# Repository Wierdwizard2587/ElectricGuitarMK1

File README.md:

# Electronic Guitar MK1

> A self-built, digitally-enhanced electric guitar featuring onboard effects, audio output and removable battery supply all integrated within a custom made Guitar.

---

## TL;DR Overview

- DIY portable electric guitar with integrated digital effects and modular power/audio system  
- Final version features Teensy 4.0, onboard FX, rotary encoder UI, OLED display, amp/speaker output, battery or DC power, and RGB lighting  
- Entire build: woodwork, PCBs, 3D prints, firmware, and more  
- Early prototype (Mk0) failed due to poor electrical design and overcomplex hardware, rebuilt from scratch over 12+ months with newly acquired engineering and fabrication skills  

---

## Specs (MK1)

### Hardware Features

- **Microcontroller:** Teensy 4.0 (600 MHz ARM Cortex M7, 1MB RAM)  
- **Audio Codec:** SGTL5000 via Teensy Audio Shield Rev D2  
- **Display:** 2.42" 128x64 OLED  
- **UI:** 4x rotary encoders (Adafruit I2C) with push buttons  
- **Output Options:**
  - 1W LM386 speaker amp + 8Ω speaker  
  - 3.5mm headphone jack  
  - 1/4" AUX output  
- **SD Card:** for saving and loading effect presets  

### Physical Design

- Custom red cedar guitar body with Strat-style neck and 22 frets  
- SSH passive pickup layout with 5-way selector  
- CNC acrylic panels for access and wiring  
- Modular 3D-printed brackets for internals  
- Magnetic battery bay  

### Power System

- **Battery:** 4S 18650 3500mAh Li-ion (16.8V max)  
- **BMS:** With overcharge/discharge protection  
- **Power Switching:** Automatically defaults to DC jack if plugged in  
- **Regulation:** L7805 LDO for logic, raw voltage for amp  
- **Runtime:** ~12 hours full load; much longer with optimized settings  

### RGB Lighting

- 6x WS2812B addressable LEDs  
- Controlled via UI with adjustable patterns and brightness  
- 5V from Teensy board, expandable via breakout  
- Mounted in a custom 3D enclosure with acrylic cover  
- See [Demo](https://github.com/Wierdwizard2587/ElectricGuitarMK1/raw/main/Progress%20Photos/Woodworking/IMG_9428.MOV)

### Design Decisions

- Abandoned analog FX + digipots due to impractical voltage/current handling  
- Digital FX chain implemented using Teensy Audio Library and CODEC  
- Custom single-layer PCB with JST headers for modularity  
- UI system built around I2C rotary encoders and OLED display  
- 3D-printed brackets standardized component mounting across internal assemblies  

### Tools and Processes

#### PCB Manufacturing

- **Chemical Etching:** Photoresist UV method with ferric chloride; scrapped due to accuracy and double-sided complexity  
- **CNC Milling:** Used FlatCAM to generate G-code, 3018 CNC and Candle for trace and drill cuts  

#### SMD Soldering

- **Stencil:** CNC-cut mylar sheets for paste application  
- **Soldering:** SMD components placed and reflowed on hot plate  

#### CAD and Design

- **KiCAD:** For schematic capture and board layout  
- **FreeCAD:** For PCB enclosure, LED mount, Guitar Body, Acrylic Plates/Panels and Router Jigs  

---

## Mk0 — The Failed First Attempt

The Mk0 was an ambitious retrofit of a cheap Stratocaster copy, originally sourced second-hand for $20 AUD. At the time, I had no electrical engineering knowledge and was only experienced with basic Arduino and Raspberry Pi projects.

### Body and Structural Work
- The original guitar was re-routed to fit electronics, resulting in reduced structural integrity and balance
- Body was repainted and cleaned up with minor woodworking skills from high school
- Attempted to house a Raspberry Pi, amplifier board, fans, wiring and more. all glued to plywood mounts inside the guitar

### Electronics and Power Mistakes
- Raspberry Pi 3B+ used for DSP software and effects switching via Linux keybinds
- 10x SPST buttons mapped to GPIO pins, wired manually without debounce or shielding
- Cooling: a heatsink and fan were mounted directly into the guitar body, protruding through the top
- Power: attempted to use a Makita 18V battery regulated by a voltage divider made from two 10W resistors (which exploded)
- Eventually switched to an XL6009 buck converter, mounted haphazardly on wood

### Audio and Shielding Failures
- Output sound had constant noise and interference, making the guitar unplayable
- Tried shielding the cavity with copper tape and spray enamel, but issues persisted
- Lack of analog audio knowledge led to poor layout and grounding, introducing hum and feedback

### Realization and Reset
- The experience made clear the importance of proper voltage regulation, shielding, grounding, and modular design
- Mk0 taught me the value of planning, measurement, and using the right components for audio and power
- In October 2023, I decided to scrap the build and committed to rebuilding everything from scratch

---

## The Learning Curve

To succeed with Mk1, I developed and refined skills across multiple disciplines:

- **Electrical theory and circuit design**
  - Learned core principles like Ohm’s Law, impedance, decoupling, signal paths, and analog vs digital tradeoffs by experimenting with breadboarded op-amp FX circuits and 555 timer modules.

- **Breadboarding, debugging, and perfboarding**
  - Built multiple guitar pedal-style analog effects, troubleshooting noise, biasing, and layout issues. Early soldering mistakes taught me good pad heating, proper joint inspection, and signal path discipline.

- **Custom PCB manufacturing**

  - *Chemical etching:* Photoresist and ferric chloride techniques worked for simple single-sided boards, but alignment and etch consistency were poor for complex layouts.

https://github.com/user-attachments/assets/e00821a1-996f-4fed-b84c-7d602e0a9be1

  - *CNC milling:* FlatCAM used to generate G-code from KiCAD Gerbers. I used a 3018 CNC with Candle to reliably cut traces and drill holes. Ultimately switched to ordered boards for reliability.

https://github.com/user-attachments/assets/3b78b966-fe12-4d0b-8b32-34254987f5ec

- **SMD workflow and hot plate reflow soldering**
  - Designed and cut my own mylar stencils for solder paste, allowing for precise paste application and fast assembly of SMD components on the hot plate.

- **Power systems and battery safety**
  - Studied Li-ion cell characteristics, pack balancing, protection circuits, and BMS behavior. Designed a 4S pack system with safe cutoff and swappable magnetic connection.

- **CAD and fabrication**
  - *KiCAD:* Used to design full schematics and board layouts with JST headers and part footprints.

  - *FreeCAD:* Modeled body routing templates, control panel shapes, bracket mounting, and tolerance-critical neck fits.

- **CNC woodworking and mechanical precision**
  - Created tight-fitting neck pockets and pickup cutouts with minimal play, ensuring mechanical stability and alignment.

Each step of the learning process fed directly into the reliability and performance of the final Mk1 design.

---

## Final Words

This project started with a failed experiment and turned into a comprehensive learning journey in electrical engineering, embedded systems, and digital fabrication. Every element—hardware, software, and mechanical—was designed, built, and tested from scratch with the goal of making a fully integrated, self-contained electric guitar. I am very proud of what I was able to accomplish and am very excited to now use and build this new knowledge and gained abilitys to even bigger and better things!

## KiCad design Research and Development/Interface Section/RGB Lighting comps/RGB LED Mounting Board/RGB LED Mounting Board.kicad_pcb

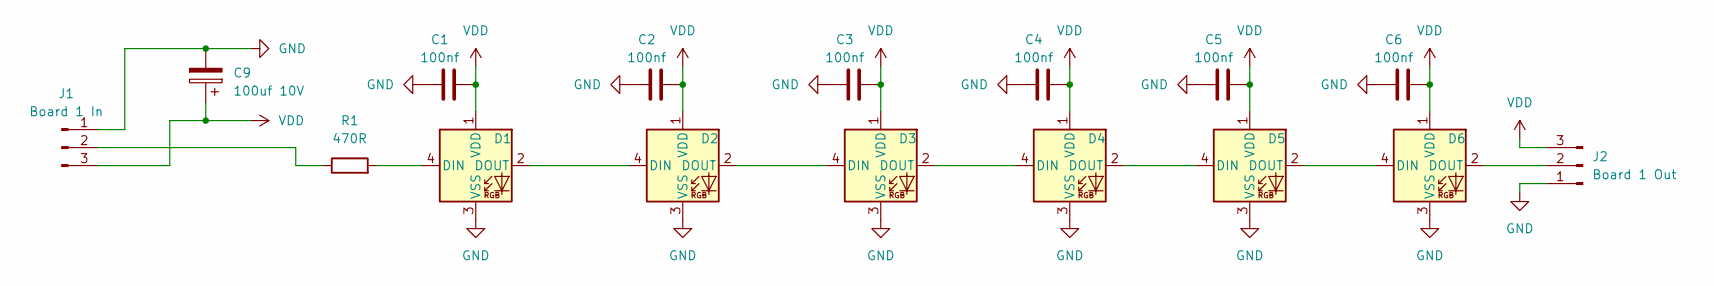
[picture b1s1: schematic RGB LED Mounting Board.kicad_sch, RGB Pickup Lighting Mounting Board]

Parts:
C1, C2, C3, C4, C5, C6: 100nf; C_1206_3216Metric
C9: 100uf 10V; CP_Elec_5x5.4
D1, D2, D3, D4, D5, D6: WS2812B; LED_WS2812B_PLCC4_5.0x5.0mm_P3.2mm
J1: Board 1 In; JST_GH_BM03B-GHS-TBT_1x03-1MP_P1.25mm_Vertical
J2: Board 1 Out; JST_GH_BM03B-GHS-TBT_1x03-1MP_P1.25mm_Vertical
R1: 470R; R_1206_3216Metric

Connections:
GND: C1.1, C2.1, C3.1, C4.1, C5.1, C6.1, C9.2, D1.3 (VSS), D2.3 (VSS), D3.3 (VSS), D4.3 (VSS), D5.3 (VSS), D6.3 (VSS), J1.1, J2.1
unnamed: D1.4 (DIN), R1.2
unnamed: D1.2 (DOUT), D2.4 (DIN)
unnamed: D2.2 (DOUT), D3.4 (DIN)
unnamed: D3.2 (DOUT), D4.4 (DIN)
unnamed: D4.2 (DOUT), D5.4 (DIN)
unnamed: D5.2 (DOUT), D6.4 (DIN)
unnamed: D6.2 (DOUT), J2.2
unnamed: J1.2, R1.1
VDD: C1.2, C2.2, C3.2, C4.2, C5.2, C6.2, C9.1, D1.1 (VDD), D2.1 (VDD), D3.1 (VDD), D4.1 (VDD), D5.1 (VDD), D6.1 (VDD), J1.3, J2.3

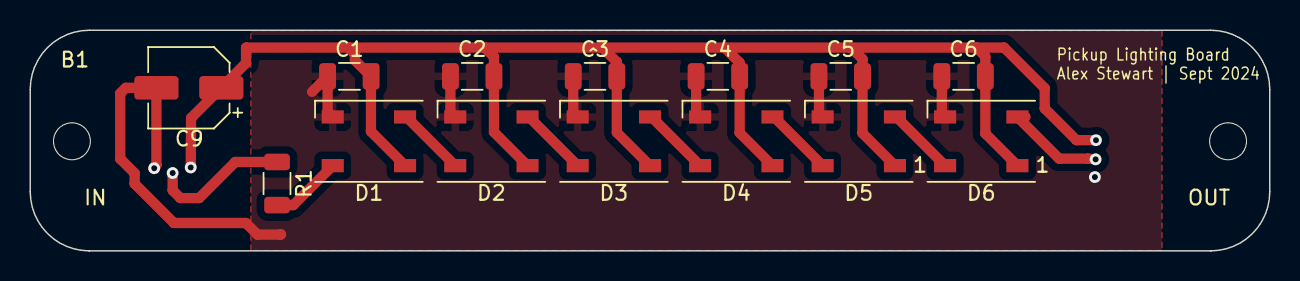
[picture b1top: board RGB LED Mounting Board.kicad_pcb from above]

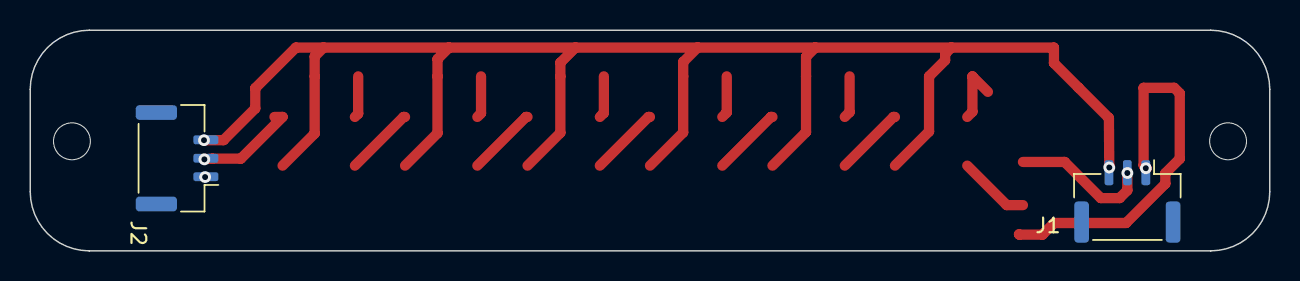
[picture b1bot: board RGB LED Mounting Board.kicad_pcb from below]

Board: 2 copper layers, 84.0 x 14.9 mm, 16 parts (2 on the bottom side), 10 nets.

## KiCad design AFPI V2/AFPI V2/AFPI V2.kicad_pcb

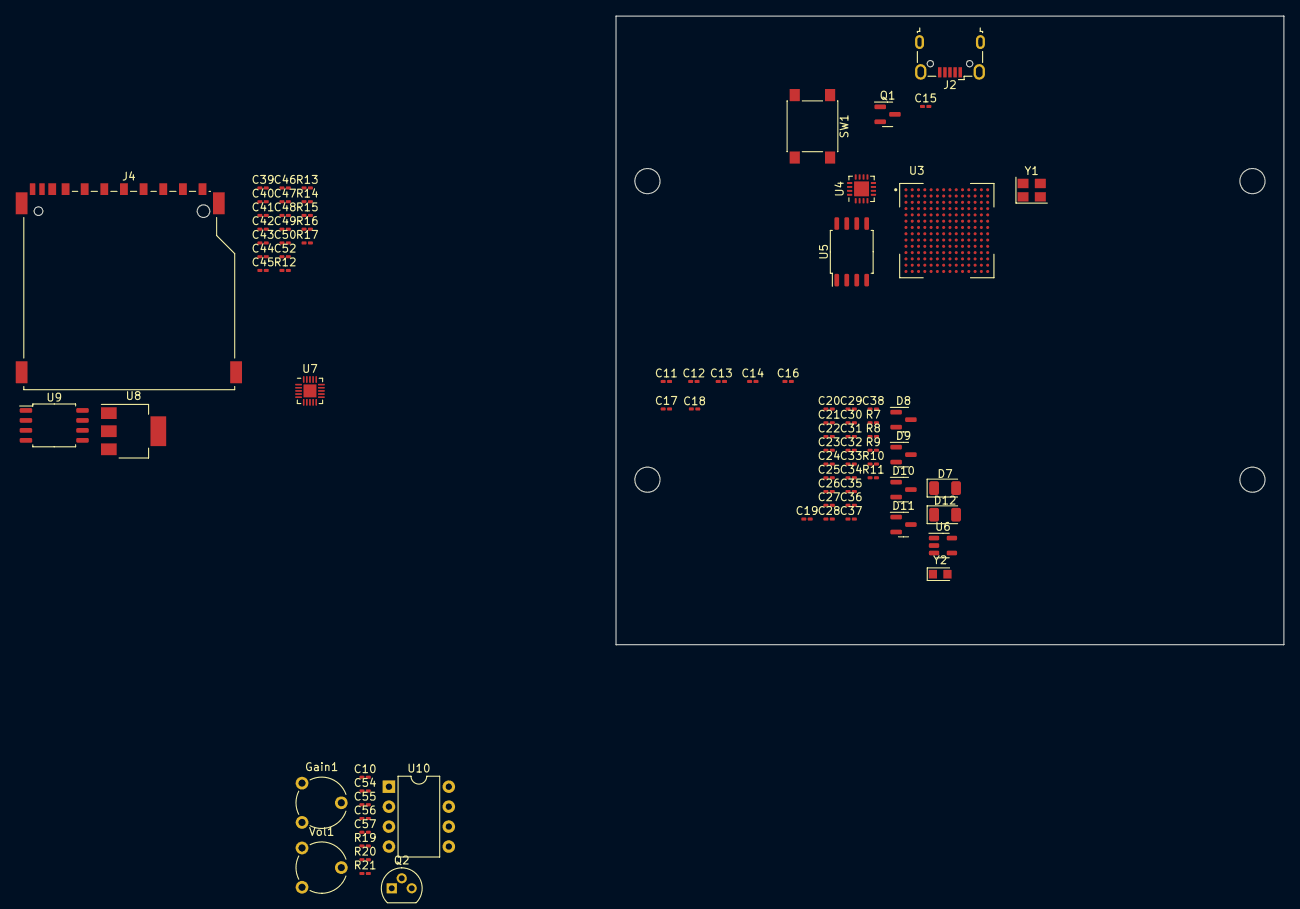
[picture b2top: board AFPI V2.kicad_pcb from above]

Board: 4 copper layers, 85.0 x 80.0 mm, 83 parts (0 on the bottom side), 70 nets, no tracks yet.

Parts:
C10, C56: 47n; C_0201_0603Metric_Pad0.64x0.40mm_HandSolder
C11, C12: 12pF; C_0201_0603Metric_Pad0.64x0.40mm_HandSolder
C13, C14: 20pF; C_0201_0603Metric_Pad0.64x0.40mm_HandSolder
C15, C22, C41, C42, C45, C46, C47, C48, C50, C52: 2.2uF; C_0201_0603Metric_Pad0.64x0.40mm_HandSolder
C16, C17, C19, C20, C23, C27, C30, C32, C33, C34, C36, C38: 0.22uF; C_0201_0603Metric_Pad0.64x0.40mm_HandSolder
C18, C26: 10nF; C_0201_0603Metric_Pad0.64x0.40mm_HandSolder
C21, C24, C28, C35, C37: 4.7uF; C_0201_0603Metric_Pad0.64x0.40mm_HandSolder
C25, C29, C31: 10uF; C_0201_0603Metric_Pad0.64x0.40mm_HandSolder
C39, C40, C43, C49: 0.1uF; C_0201_0603Metric_Pad0.64x0.40mm_HandSolder
C44: 0.15uF; C_0201_0603Metric_Pad0.64x0.40mm_HandSolder
C54: 100u; C_0201_0603Metric_Pad0.64x0.40mm_HandSolder
C55: 100n; C_0201_0603Metric_Pad0.64x0.40mm_HandSolder
C57: 220u; C_0201_0603Metric_Pad0.64x0.40mm_HandSolder
D7, D12: LED; D_1206_3216Metric
D8, D9, D10, D11: BAT54C; SOT-23
Gain1: 1kB; Potentiometer_Piher_PT-6-V_Vertical
J2: USB Micro-B; USB_Micro-B_Wuerth_629105150521
J4: Micro_SD_Card; SD_TE_2041021
Q1: DMG2305UX; SOT-23
Q2: MPF102; TO-92
R7, R11: 470; C_0201_0603Metric_Pad0.64x0.40mm_HandSolder
R8: 2.2M; C_0201_0603Metric_Pad0.64x0.40mm_HandSolder
R9, R10: 100k; C_0201_0603Metric_Pad0.64x0.40mm_HandSolder
R12, R15, R16: 2.2k; C_0201_0603Metric_Pad0.64x0.40mm_HandSolder
R13, R14: 10k; C_0201_0603Metric_Pad0.64x0.40mm_HandSolder
R17: 100; C_0201_0603Metric_Pad0.64x0.40mm_HandSolder
R19: 1M5; C_0201_0603Metric_Pad0.64x0.40mm_HandSolder
R20: 3k9; C_0201_0603Metric_Pad0.64x0.40mm_HandSolder
R21: 10R; C_0201_0603Metric_Pad0.64x0.40mm_HandSolder
SW1: SW_DIP_x01; SW_Push_1P1T_NO_6x6mm_H9.5mm
U3: MIMXRT1062DVJ6B; BGA196C80P14X14_1200X1200X152N
U4: MKL02Z32VFG4; QFN-16-1EP_3x3mm_P0.5mm_EP1.9x1.9mm
U5: W25Q64; SOIC-8_5.23x5.23mm_P1.27mm
U6: TLV75733PDBV; SOT-23-5
U7: SGTL5000XNLA3; QFN-20-1EP_3x3mm_P0.4mm_EP1.65x1.65mm
U8: AP7313; SOT-223-3_TabPin2
U9: W25Q128JVS; SOIC-8_5.23x5.23mm_P1.27mm
U10: LM386; DIP-8_W7.62mm
Vol1: 10kB; Potentiometer_Piher_PT-6-V_Vertical
Y1: 24MHz; Crystal_SMD_3225-4Pin_3.2x2.5mm
Y2: 32.768kHz; Crystal_SMD_TXC_9HT11-2Pin_2.0x1.2mm_HandSoldering

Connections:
3.3V Pin: C18.1, C19.1, C20.1, C21.1, C22.1, C38.2, C39.1, C40.1, C41.1, D9.2 (A), D12.2 (A), J4.4 (VDD), R9.1, R13.1, R14.1, R15.2, R16.1, U3.E6 (NVCC_EMC), U3.E9 (NVCC_GPIO), U3.F5 (NVCC_EMC), U3.F10 (NVCC_GPIO), U3.J6 (NVCC_SD0), U3.J10 (NVCC_GPIO), U3.K4 (DCDC_IN_Q), U3.K5 (NVCC_SD1), U3.N14 (VDDA_ADC_3P3), U3.P12 (VDD_HIGH_IN), U4.1 (VDD/VREFH), U5.8 (VCC), U6.5 (OUT), U7.12 (VDDIO), U8.1 (VI), U9.3 (IO2), U9.7 (IO3), U9.8 (VCC)
+9V: C54.1, Q2.1 (D), U10.6 (V+)
DCDC_IN: C23.1, C24.1, C25.1, U3.L1 (DCDC_IN), U3.L2 (DCDC_IN)
DCDC_LP: U3.M1 (DCDC_LP), U3.M2 (DCDC_LP)
DN: C16.1, C17.1, J2.2, J2.3, Q1.2 (S), U3.L8 (USB_OTG1_DP), U3.M8 (USB_OTG1_DN), U3.N6 (USB_OTG1_VBUS), U3.P6 (USB_OTG2_VBUS), U6.1 (IN)
GND Pin: C11.1, C12.1, C13.1, C14.1, C15.1, C16.2, C17.2, C18.2, C19.2, C20.2, C21.2, C22.2, C23.2, C24.2, C25.2, C26.2, C27.2, C28.2, C29.2, C30.2, C31.2, C32.2, C33.2, C34.2, C35.2, C36.2, C37.2, C38.1, C39.2, C40.2, C41.2, C42.2, C43.2, C44.1, C50.2, C52.2, C54.2, C55.2, C56.1, D7.1 (K), J2.5, J4.6 (VSS), Q1.1 (G), R8.1, R10.2, R19.2, R20.2, SW1.2, U3.A1 (VSS), U3.A14 (VSS), U3.B5 (VSS), U3.B10 (VSS), U3.E2 (VSS), U3.E13 (VSS), U3.G7 (VSS), U3.G8 (VSS), U3.H7 (VSS), U3.H8 (VSS), U3.J7 (VSS), U3.J8 (VSS), U3.K2 (VSS), U3.K13 (VSS), U3.L9 (VSS), U3.N1 (DCDC_GND), U3.N2 (DCDC_GND), U3.N5 (VSS), U3.N8 (VSS), U3.P1 (VSS), U3.P14 (VSS), U4.2 (VSS/VREFL), U4.17 (EPAD), U5.4 (GND), U6.2 (GND), U7.21 (GND), U8.2 (GND), U9.4 (GND), U10.3 (+), U10.4 (GND), Vol1.3, Y1.2, Y1.4
GPIO 6: R13.2, U3.D9 (GPIO_B0_10), U9.2 (DO(IO1))
GPIO 7: U3.B11 (GPIO_B1_01), U7.17 (I2S_DIN)
GPIO 8: U3.A11 (GPIO_B1_00), U7.16 (I2S_DOUT)
GPIO 10: J4.2 (DAT3/CD), R14.2, U3.D7 (GPIO_B0_00)
GPIO 11: J4.3 (CMD), U3.E8 (GPIO_B0_02), U9.1 (~CS)
GPIO 12: J4.7 (DAT0), U3.E7 (GPIO_B0_01), U9.5 (DI(IO0))
GPIO 13: J4.5 (CLK), R7.2, U3.D8 (GPIO_B0_03), U9.6 (CLK)
GPIO 18 / A4: R16.2, U3.K11 (GPIO_AD_B1_01), U7.18 (CTRL_DATA)
GPIO 19 / A5: R15.1, U3.J11 (GPIO_AD_B1_00), U7.19 (CTRL_CLK)
GPIO 20 / A6: U3.L13 (GPIO_AD_B1_10), U7.14 (I2S_LRCLK)
GPIO 21 / A7: U3.J13 (GPIO_AD_B1_11), U7.15 (I2S_SCLK)
GPIO 23 / A9: R17.1, U3.M13 (GPIO_AD_B1_09)
K7: R9.2, U3.K7 (PMIC_ON_REQ), U6.3 (EN)
K8: C31.1, C32.1, D10.2 (A), U3.K8 (VDD_USB_CAP)
M9: C30.1, D8.1 (K), D9.1 (K), D10.1 (K), D11.1 (K), U3.M9 (VDD_SNVS_IN)
M10: C33.1, U3.M10 (VDD_SNVS_CAP)
N9: C13.2, U3.N9 (RTC_XTALI), Y2.1
N11: C12.2, U3.N11 (XTALO), Y1.3
unnamed: C10.1, Vol1.1
unnamed: C56.2, R21.2
unnamed: C57.1, R21.1, U10.5
unnamed: D7.2 (A), R7.1
unnamed: D12.1 (K), R11.1
unnamed: Gain1.1, U10.1 (GAIN)
unnamed: Gain1.2, Gain1.3, U10.8 (GAIN)
unnamed: C15.2, J2.1
unnamed: C49.1, R12.1
unnamed: Q2.3 (G), R19.1
unnamed: C10.2, Q2.2 (S), R20.1
unnamed: U3.F11 (GPIO_AD_B0_04), U4.4 (PTA4)
unnamed: U3.E14 (GPIO_AD_B0_06), U4.5 (PTA5)
unnamed: U3.F12 (GPIO_AD_B0_07), U4.8 (PTB0/IRQ_5)
unnamed: U3.F13 (GPIO_AD_B0_08), U4.13 (PTB5/IRQ_12)
unnamed: U3.F14 (GPIO_AD_B0_09), U4.7 (PTA7/IRQ_4)
unnamed: U3.G13 (GPIO_AD_B0_10), U4.6 (PTA6)
unnamed: U3.L3 (GPIO_SD_B1_06), U5.1 (~CS)
unnamed: U3.L4 (GPIO_SD_B1_07), U5.6 (CLK)
unnamed: U3.P3 (GPIO_SD_B1_08), U5.5 (DI(IO0))
unnamed: U3.N4 (GPIO_SD_B1_09), U5.2 (DO(IO1))
unnamed: U3.P4 (GPIO_SD_B1_10), U5.3 (IO2)
unnamed: U3.P5 (GPIO_SD_B1_11), U5.7 (IO3)
unnamed: C48.2, U7.9 (LINEIN_L)
unnamed: C47.2, U7.8 (LINEIN_R)
unnamed: C46.1, U7.7 (LINEOUT_L)
unnamed: C45.1, U7.6 (LINEOUT_R)
unnamed: C49.2, U7.10 (MIC)
unnamed: C50.1, R12.2, U7.11 (MIC_BIAS)
unnamed: R17.2, U7.13 (SYS_MCLK)
unnamed: C44.2, U7.5 (VAG)
unnamed: C42.1, C43.1, U7.3 (VDDA)
unnamed: C52.1, U7.20 (VDDD), U8.3 (VO)
unnamed: U10.2 (-), Vol1.2
unnamed: C55.1, U10.7 (BYPASS)
P8: C36.1, C37.1, U3.P8 (VDD_HIGH_CAP)
P9: C14.2, U3.P9 (RTC_XTALO), Y2.2
P10: C34.1, C35.1, U3.P10 (NVCC_PLL)
P11: C11.2, R8.2, U3.P11 (XTALI), Y1.1
PTA1: U3.F3 (GPIO_EMC_01), U4.15 (PTA1/IRQ_1/LPTMR0_ALT1)
PTA3: R10.1, U3.G10 (GPIO_AD_B0_11), U3.K3 (DCDC_PSWITCH), U4.3 (PTA3)
PTB1: U3.M7 (POR_B), U4.9 (PTB1/IRQ_6)
PTB3: R11.2, U4.11 (PTB3/IRQ_10)
PTB4: U3.D10 (GPIO_B0_13), U4.12 (PTB4/IRQ_11)
Prog Pin: SW1.1, U4.10 (PTB2/IRQ_7)
VDD_SOC_IN: C26.1, C27.1, C28.1, C29.1, U3.F6 (VDD_SOC_IN), U3.F7 (VDD_SOC_IN), U3.F8 (VDD_SOC_IN), U3.F9 (VDD_SOC_IN), U3.G6 (VDD_SOC_IN), U3.G9 (VDD_SOC_IN), U3.H6 (VDD_SOC_IN), U3.H9 (VDD_SOC_IN), U3.J5 (DCDC_SENSE), U3.J9 (VDD_SOC_IN)

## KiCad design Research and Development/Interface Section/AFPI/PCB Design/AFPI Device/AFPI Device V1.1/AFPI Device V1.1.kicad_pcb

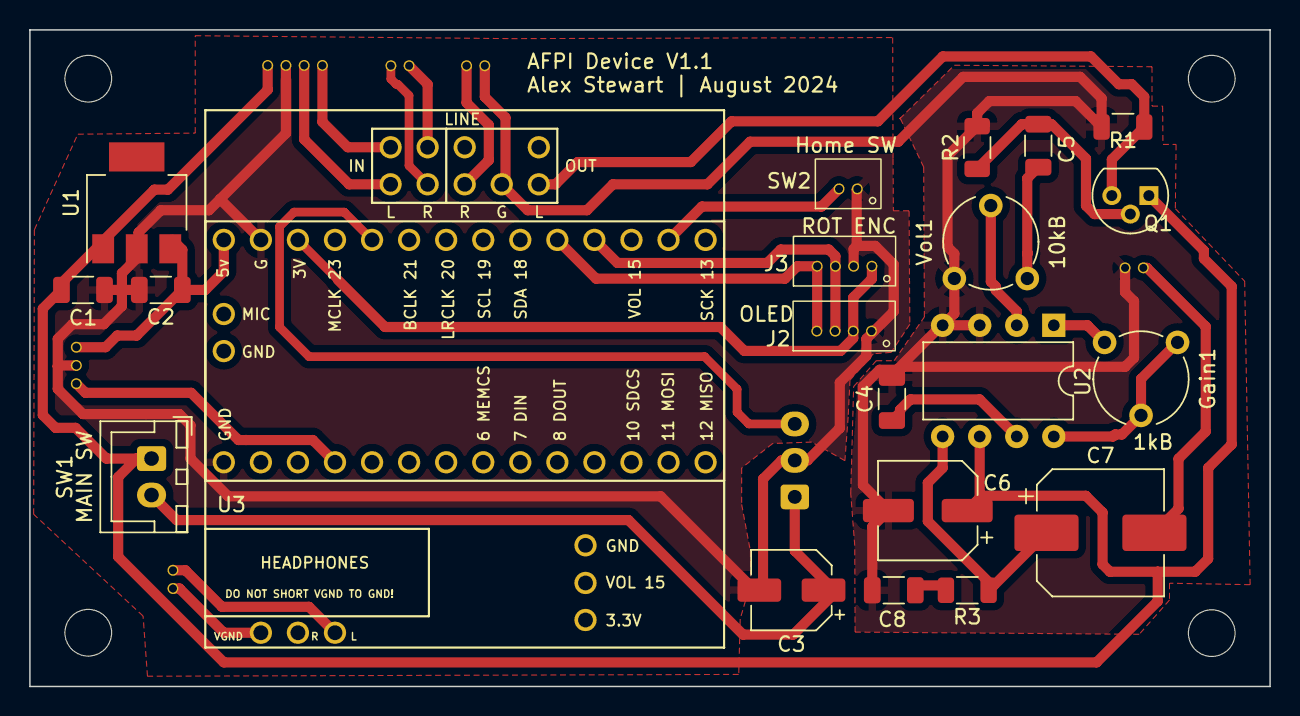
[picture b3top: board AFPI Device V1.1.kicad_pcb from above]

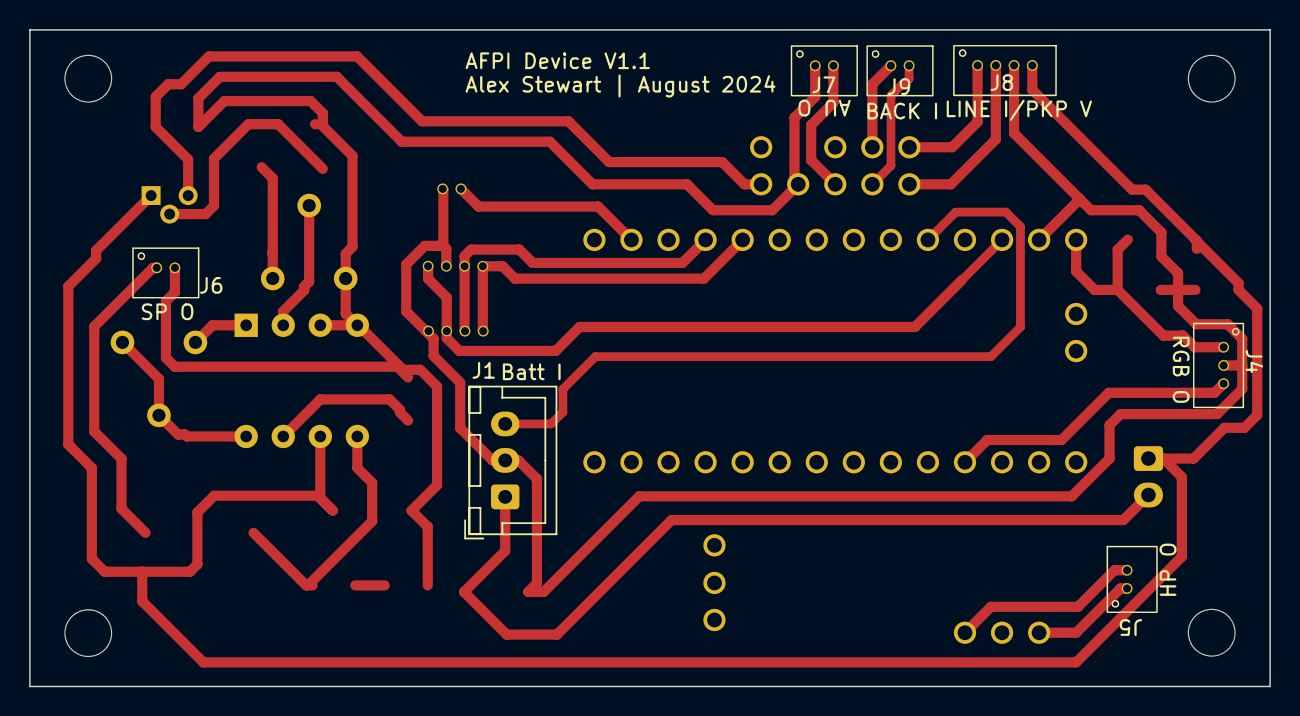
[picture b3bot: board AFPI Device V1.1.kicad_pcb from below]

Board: 2 copper layers, 85.0 x 45.0 mm, 28 parts (7 on the bottom side), 28 nets.

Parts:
C1: 330nf; C_1206_3216Metric
C2: 100nf; C_1206_3216Metric
C3: 10uf 35V; CP_Elec_5x5.4
C4: 100n; C_1206_3216Metric
C5, C8: 47n; C_1206_3216Metric
C6: 100u; CP_Elec_6.3x7.7
C7: 220u; CP_Elec_8x10.5
Gain1: 1kB; Potentiometer_Piher_PT-6-V_Vertical
J1: Batt I; JST_XH_B3B-XH-A_1x03_P2.50mm_Vertical
J2: OLED; JST 1.25mm THT 01x04
J3: ROT ENC; JST 1.25mm THT 01x04
J4: RGB O; JST 1.25mm THT 01x03
J5: HP O; JST 1.25mm THT 01x02
J6: SP O; JST 1.25mm THT 01x02
J7: AU O; JST 1.25mm THT 01x02
J8: LINE I/PKP V; JST 1.25mm THT 01x04
J9: BACK I; JST 1.25mm THT 01x02
Q1: MPF102; TO-92
R1: 1M5; R_1206_3216Metric
R2: 3k9; R_1206_3216Metric
R3: 10R; R_1206_3216Metric
SW1: MAIN SW; JST_XH_B2B-XH-A_1x02_P2.50mm_Vertical
SW2: Home SW; JST 1.25mm THT 01x02
U1: L7805; SOT-223
U2: LM386; DIP-8_W7.62mm
U3: Teensy4.0_AudioShield_REVD; Teensy 4.0 audioshield
Vol1: 10kB; Potentiometer_Piher_PT-6-V_Vertical

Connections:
+3.3V: J2.2, J3.1, U3.28 (3V)
+5V: C2.1, J4.1, U1.3 (OUT), U3.30 (5V)
+9V: C1.1, C6.1, J8.4, Q1.1 (D), SW1.1 (A), U1.1 (IN), U2.6 (V+)
Batt Vref: J1.3, U3.26 (22_A8_CTX1)
GND: C1.2, C2.2, C3.2, J1.2, J2.1, J3.2, J4.2, J8.3, SW2.1 (A), U1.2 (GND), U3.1 (GND), U3.29 (GND)
GND1: C4.2, C6.2, C8.1, J6.2, J7.1, R1.2, R2.2, U2.3 (+), U2.4 (GND), U3.32 (LINE_OUT_GND), Vol1.3
HP Line: J5.2, U3.41 (HEADPHONES_L)
HP VGND: J5.1, U3.43 (HEADPHONES_VGND)
Line OUT R: J7.2, U3.33 (LINE_OUT_R)
Line in R: J9.2, U3.34 (LINE_IN_R)
Line in R GND: J9.1, U3.36 (LINE_IN_R_GND)
unnamed: C5.1, Vol1.1
unnamed: C7.1, R3.1, U2.5
unnamed: C8.2, R3.2
unnamed: Gain1.1, U2.1 (GAIN)
unnamed: Gain1.2, Gain1.3, U2.8 (GAIN)
unnamed: C3.1, J1.1, SW1.2 (B)
unnamed: C7.2, J6.1
unnamed: J8.1, U3.37 (LINE_IN_L_GND)
unnamed: J8.2, U3.35 (LINE_IN_L)
unnamed: Q1.3 (G), R1.1, U3.31 (LINE_OUT_L)
unnamed: C5.2, Q1.2 (S), R2.1
unnamed: SW2.2 (B), U3.18 (14_A0_TX3_SPDIF_OUT)
unnamed: U2.2 (-), Vol1.2
unnamed: C4.1, U2.7 (BYPASS)
Pin 2: J4.3, U3.4 (2_OUT2)
Pin 16 SCL1: J2.3, J3.3, U3.20 (16_A2_RX4_SCL1)
Pin 17 SDA1: J2.4, J3.4, U3.21 (17_A3_TX4_SDA1)

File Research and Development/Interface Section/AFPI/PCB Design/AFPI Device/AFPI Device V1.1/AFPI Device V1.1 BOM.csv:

"Id";"Designator";"Footprint";"Quantity";"Designation";"Supplier and ref";
1;"C1";"C_1206_3216Metric";1;"330nf";;;
2;"C5,C8";"C_1206_3216Metric";2;"47n";;;
3;"C2";"C_1206_3216Metric";1;"100nf";;;
4;"Gain1";"Potentiometer_Piher_PT-6-V_Vertical";1;"1kB";;;
5;"SW1";"JST_XH_B2B-XH-A_1x02_P2.50mm_Vertical";1;"MAIN SW";;;
6;"J2";"JST 1.25mm THT 01x04";1;"OLED";;;
7;"Vol1";"Potentiometer_Piher_PT-6-V_Vertical";1;"10kB";;;
8;"R1";"R_1206_3216Metric";1;"1M5";;;
9;"C6";"CP_Elec_6.3x7.7";1;"100u";;;
10;"J3";"JST 1.25mm THT 01x04";1;"ROT ENC ";;;
11;"C3";"CP_Elec_5x5.4";1;"10uf 35V";;;
12;"U1";"SOT-223";1;"L7805";;;
13;"C7";"CP_Elec_8x10.5";1;"220u";;;
14;"R2";"R_1206_3216Metric";1;"3k9";;;
15;"R3";"R_1206_3216Metric";1;"10R";;;
16;"SW2";"JST 1.25mm THT 01x02";1;"Home SW";;;
17;"U3";"Teensy 4.0 audioshield";1;"Teensy4.0_AudioShield_REVD";;;
18;"U2";"DIP-8_W7.62mm";1;"LM386";;;
19;"C4";"C_1206_3216Metric";1;"100n";;;
20;"Q1";"TO-92";1;"MPF102";;;
21;"J9";"JST 1.25mm THT 01x02";1;"BACK I";;;
22;"J6";"JST 1.25mm THT 01x02";1;"SP O";;;
23;"J1";"JST_XH_B3B-XH-A_1x03_P2.50mm_Vertical";1;"Batt I";;;
24;"J5";"JST 1.25mm THT 01x02";1;"HP O";;;
25;"J8";"JST 1.25mm THT 01x04";1;"LINE I/PKP V";;;
26;"J7";"JST 1.25mm THT 01x02";1;"AU O";;;
27;"J4";"JST 1.25mm THT 01x03";1;"RGB O";;;

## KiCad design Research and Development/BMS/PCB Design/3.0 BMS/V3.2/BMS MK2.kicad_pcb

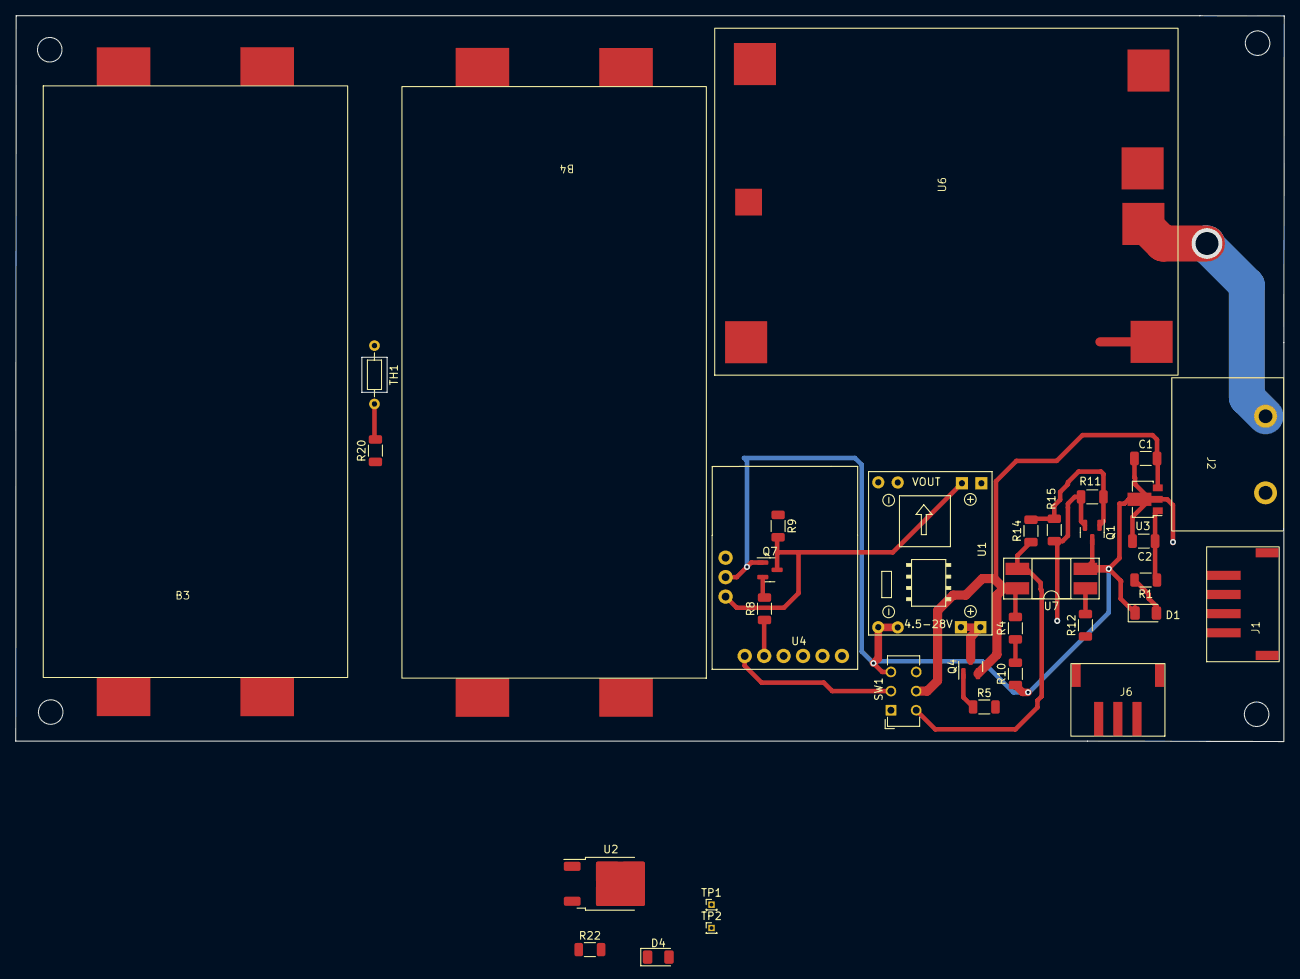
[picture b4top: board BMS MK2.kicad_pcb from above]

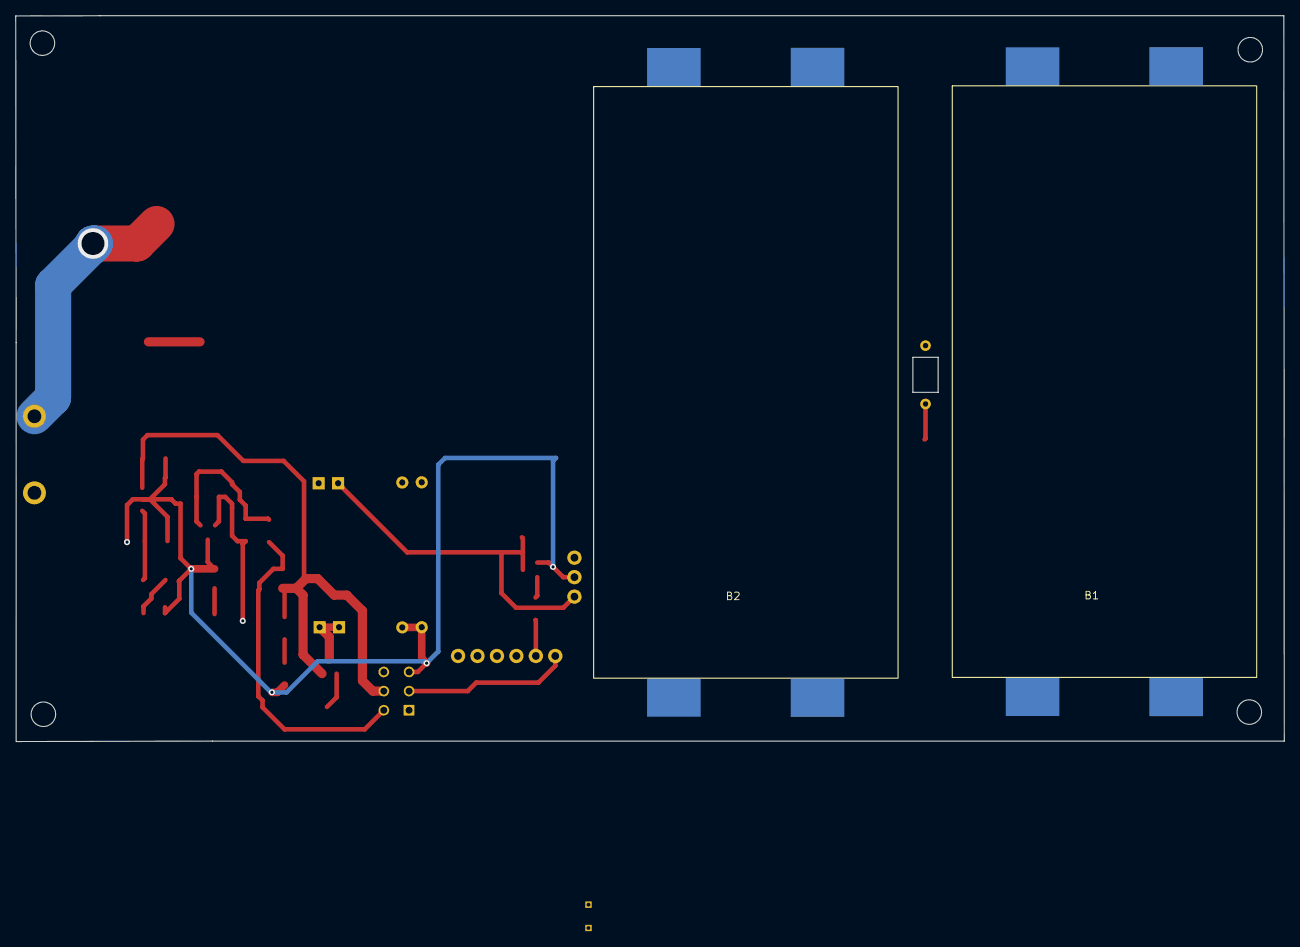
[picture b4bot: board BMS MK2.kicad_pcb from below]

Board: 2 copper layers, 165.7 x 94.8 mm, 36 parts (2 on the bottom side), 26 nets.

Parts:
B1, B2, B3, B4: 18650 Batt 2S Holder
C1, C2: C; C_1206_3216Metric
D1: ON LED; LED_1206_3216Metric
D4: CHG LED; LED_1206_3216Metric
J1: PWR LOAD OUT; XH 2.54mm 4p vertical header
J2: B CHG IN; kf1000 screw terminal
J6: load chg in; XH 2.54mm 3p smd vertical header
Q1: AO3400A; SOT-23
Q4: AO3407; SOT-23
Q7: PN100; SOT-23
R1, R22: R; R_1206_3216Metric
R4, R9, R10, R14, R15, R20: 10K; R_1206_3216Metric
R5: 1.2K; R_1206_3216Metric
R8: 3k3; R_1206_3216Metric
R11: 100K; R_1206_3216Metric
R12: 430R; R_1206_3216Metric
SW1: SW_DPDT_x2; SW_CuK_JS202011CQN_DPDT_Straight
TH1: Thermistor; R_Axial_DIN0204_L3.6mm_D1.6mm_P7.62mm_Horizontal
TP1: B+; PinHeader_1x01_P1.00mm_Vertical
TP2: B-; PinHeader_1x01_P1.00mm_Vertical
U1: MP1584; SRT_MPT1584EN_Module
U2: AOD409; TO-252-2
U3: L78L05_SOT89; SOT-89-3
U4: ATTiny 85 Module; Digispark attiny85 board
U6: 4s Batt Protect Module; BMS 4S Module
U7: PC817; DIP-4_W8.89mm_SMDSocket_LongPads

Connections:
5v attiny out: R20.1, U4.1 (5V)
+9V: Q7.3 (C), R9.2, U1.3 (OUT+), U4.3 (VIN)
+12V: J6.3, Q4.3 (D), R5.2, U1.1 (IN+)
+BATT: C1.2, Q4.2 (S), R4.2, R22.1, SW1.5 (B), TP1.1, U2.2 (D), U3.3 (IN), U6.1 (P+), U7.4
+VDC: J2.2, U2.3 (S)
-12V: C1.1, C2.1, D1.1 (K), J1.1, J6.2, Q1.3 (D), Q7.1 (E), R10.1, SW1.3 (C), TH1.1, U1.2 (IN-), U1.4 (OUT-), U3.2 (GND), U4.2 (GND), U7.2
-BATT: D4.1 (K), J2.1, Q1.2 (S), R11.1, R15.2, TP2.1, U6.2 (P-)
Batt SW VCC: R12.1, U4.8 (P4)
Battery Vref: J1.3, J6.1, R4.1, R10.2, U4.7 (P3)
CGE SW V+: R9.1, U2.1 (G)
unnamed: B1.1 (B1+), B1.3 (B2+), B2.2 (B1-), B2.4 (B2-), U6.4 (4.2V)
unnamed: B1.2 (B1-), B1.4 (B2-), U6.3 (0V)
unnamed: B2.1 (B1+), B2.3 (B2+), B3.2 (B1-), B3.4 (B2-), U6.5 (8.4V)
unnamed: B3.1 (B1+), B3.3 (B2+), B4.2 (B1-), B4.4 (B2-), U6.6 (12.6V)
unnamed: B4.1 (B1+), B4.3 (B2+), U6.7 (16.8V)
unnamed: D1.2 (A), R1.2
unnamed: D4.2 (A), R22.2
unnamed: Q1.1 (G), R11.2, R14.2, R15.1
unnamed: Q7.2 (B), R8.2
unnamed: R12.2, U7.1
unnamed: SW1.2 (B), U4.4 (P0)
unnamed: R14.1, SW1.4 (A), U7.3
unnamed: C2.2, R1.1, U3.1 (OUT)
unnamed: R8.1, U4.5 (P1)
unnamed: R20.2, TH1.2, U4.6 (P2)
VD: J1.4, Q4.1 (G), R5.1

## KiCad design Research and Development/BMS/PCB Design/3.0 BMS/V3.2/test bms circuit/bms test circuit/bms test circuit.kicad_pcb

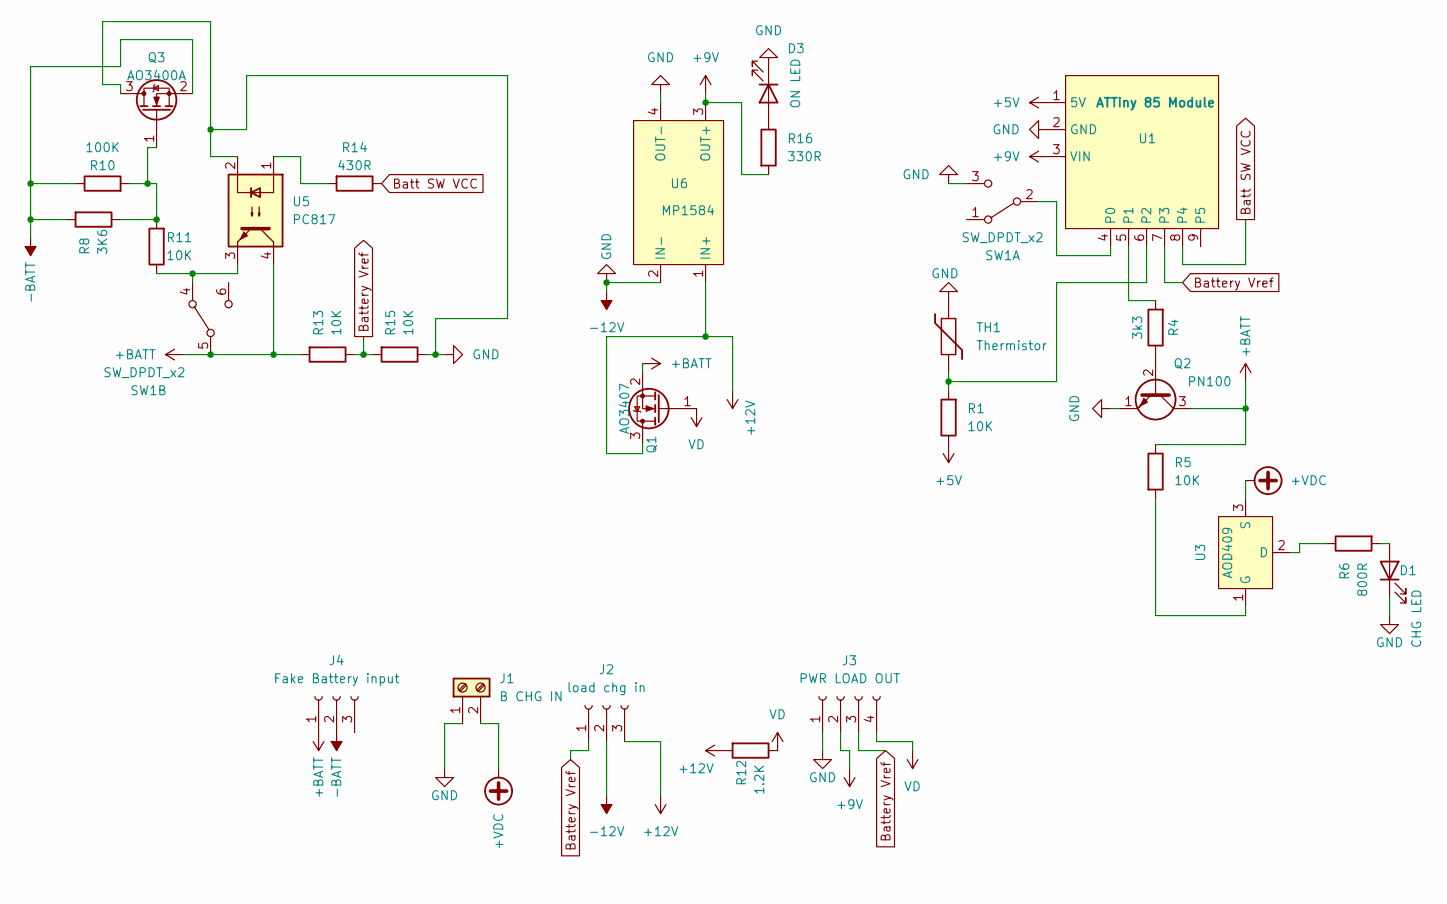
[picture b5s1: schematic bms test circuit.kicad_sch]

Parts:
D1: CHG LED; LED_1206_3216Metric
D3: ON LED; LED_1206_3216Metric
J1: B CHG IN; kf1000 screw terminal
J2: load chg in; XH 2.54mm 3p smd vertical header
J3: PWR LOAD OUT; XH 2.54mm 4p vertical header
J4: Fake Battery input; XH 2.54mm 3p smd vertical header
Q1: AO3407; SOT-23
Q2: PN100; SOT-23
Q3: AO3400A; SOT-23
R1, R5, R11, R13, R15: 10K; R_1206_3216Metric
R4: 3k3; R_1206_3216Metric
R6: 800R; R_1206_3216Metric
R8: 3K6; R_1206_3216Metric
R10: 100K; R_1206_3216Metric
R12: 1.2K; R_1206_3216Metric
R14: 430R; R_1206_3216Metric
R16: 330R; R_1206_3216Metric
SW1: SW_DPDT_x2; SW_CuK_JS202011CQN_DPDT_Straight
TH1: Thermistor; R_Axial_DIN0204_L3.6mm_D1.6mm_P7.62mm_Horizontal
U1: ATTiny 85 Module; Digispark attiny85 board
U3: AOD409; TO-252-2
U5: PC817; DIP-4_W8.89mm_SMDSocket_LongPads
U6: MP1584; SRT_MPT1584EN_Module

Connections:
+5V: R1.1, U1.1 (5V)
+9V: J3.2, R16.2, U1.3 (VIN), U6.3 (OUT+)
+12V: J2.3, Q1.3 (D), R12.2, U6.1 (IN+)
+BATT: J4.1, Q1.2 (S), Q2.3 (C), R5.1, R13.2, SW1.5 (B), U5.4
+VDC: J1.2, U3.3 (S)
-12V: D1.1 (K), D3.1 (K), J1.1, J2.2, J3.1, Q2.1 (E), Q3.3 (D), R15.1, SW1.3 (C), TH1.1, U1.2 (GND), U5.2, U6.2 (IN-), U6.4 (OUT-)
-BATT: J4.2, Q3.2 (S), R8.2, R10.1
Batt SW VCC: R14.1, U1.8 (P4)
Battery Vref: J2.1, J3.3, R13.1, R15.2, U1.7 (P3)
unnamed: D1.2 (A), R6.2
unnamed: D3.2 (A), R16.1
unnamed: Q2.2 (B), R4.1
unnamed: Q3.1 (G), R8.1, R10.2, R11.2
unnamed: R14.2, U5.1
unnamed: SW1.2 (B), U1.4 (P0)
unnamed: R11.1, SW1.4 (A), U5.3
unnamed: R4.2, U1.5 (P1)
unnamed: R1.2, TH1.2, U1.6 (P2)
unnamed: R6.1, U3.2 (D)
unnamed: R5.2, U3.1 (G)
VD: J3.4, Q1.1 (G), R12.1

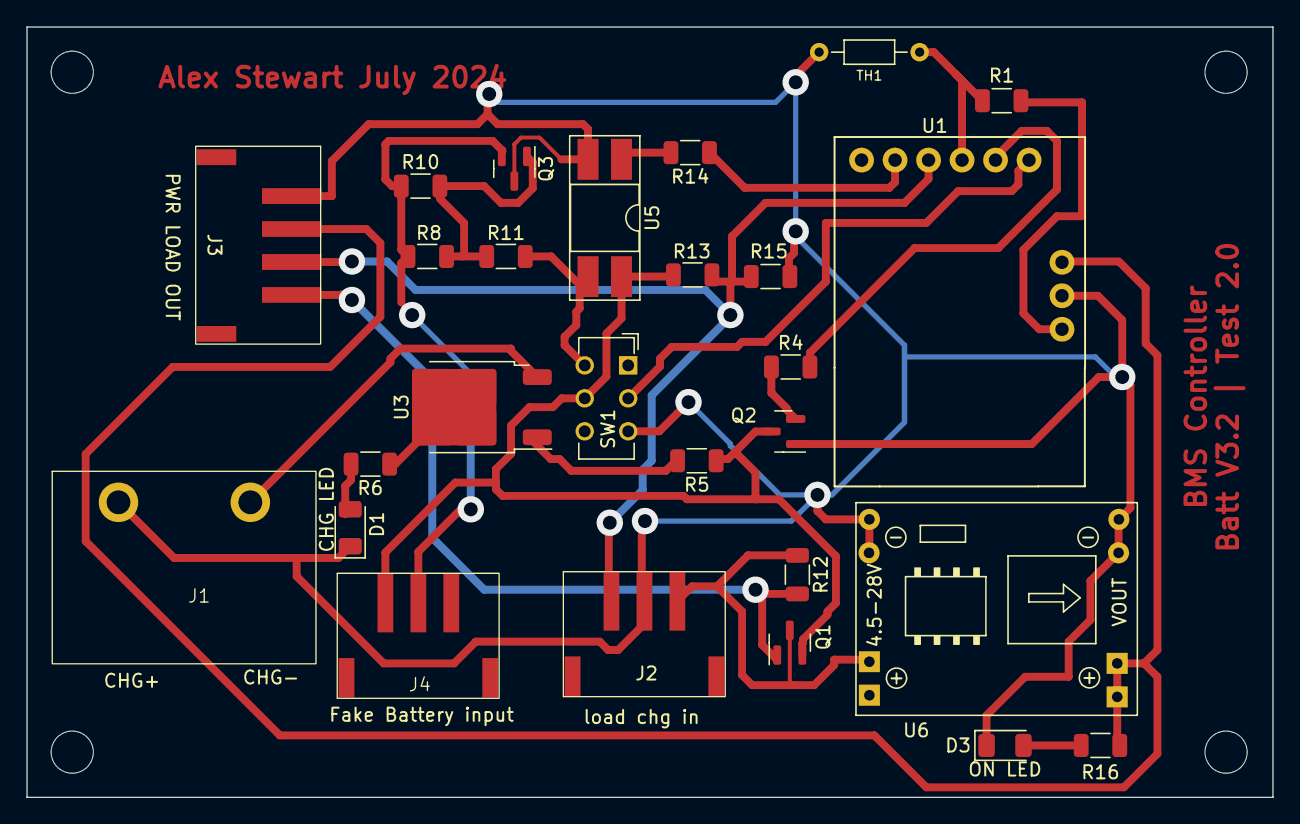
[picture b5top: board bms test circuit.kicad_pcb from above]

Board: 2 copper layers, 94.5 x 58.4 mm, 27 parts (0 on the bottom side), 21 nets.

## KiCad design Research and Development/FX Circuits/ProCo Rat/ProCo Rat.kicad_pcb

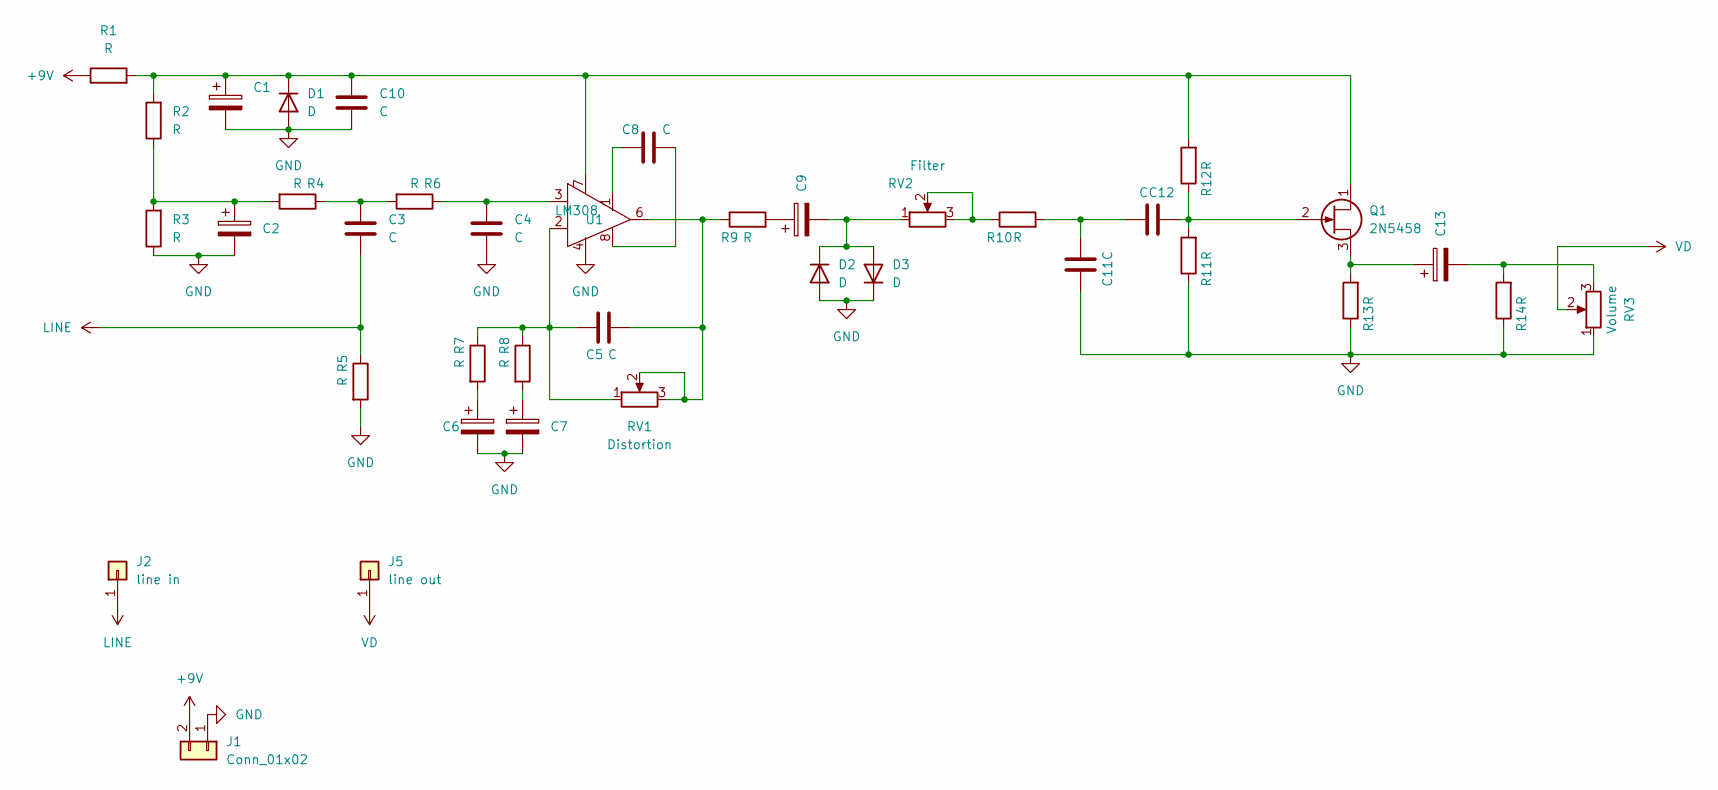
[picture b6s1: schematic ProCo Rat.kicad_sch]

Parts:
C1: C_Polarized; CP_Elec_6.3x5.4
C2, C6, C7, C9, C13: C_Polarized; CP_Elec_4x5.4
C3, C4, C5, C8, C10, C11, C12: C; C_1206_3216Metric
D1, D2, D3: D; D_1206_3216Metric
J1: Conn_01x02; PinHeader_1x02_P2.54mm_Vertical_SMD_Pin1Left
J2: line in; PinHeader_1x01_P2.54mm_Vertical
J5: line out; PinHeader_1x01_P2.54mm_Vertical
Q1: 2N5458; TO-92
R1, R2, R3, R4, R5, R6, R7, R8, R9, R10, R11, R12, R13, R14: R; R_1206_3216Metric
RV1: Distortion; XH 2.54mm 3p smd vertical header
RV2: Filter; XH 2.54mm 3p smd vertical header
RV3: Volume; XH 2.54mm 3p smd vertical header
U1: LM308; DIP-8_W7.62mm

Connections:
+9V: J1.2, R1.1
GND: C1.2, C2.2, C4.2, C6.2, C7.2, C10.2, C11.1, D1.2 (A), D2.2 (A), D3.1 (K), J1.1, R3.1, R5.2, R11.1, R13.1, R14.1, RV3.1, U1.4
LINE: C3.2, J2.1, R5.1
unnamed: C2.1, R2.1, R3.2, R4.2
unnamed: C3.1, R4.1, R6.2
unnamed: C4.1, R6.1, U1.3
unnamed: C5.1, R7.1, R8.1, RV1.1, U1.2
unnamed: C5.2, R9.1, RV1.2, RV1.3, U1.6
unnamed: C6.1, R7.2
unnamed: C7.1, R8.2
unnamed: C8.1, U1.1
unnamed: C8.2, U1.8
unnamed: C9.1, R9.2
unnamed: C11.2, C12.2, R10.2
unnamed: C13.2, R14.2, RV3.3
unnamed: C1.1, C10.1, D1.1 (K), Q1.1 (D), R1.2, R2.2, R12.2, U1.7
unnamed: C9.2, D2.1 (K), D3.2 (A), RV2.1
unnamed: C12.1, Q1.2 (G), R11.2, R12.1
unnamed: C13.1, Q1.3 (S), R13.2
unnamed: R10.1, RV2.2, RV2.3
VD: J5.1, RV3.2
